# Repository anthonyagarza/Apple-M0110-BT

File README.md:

Apple M0110 BT PCB
===================

A prototype replacement pcb for the Apple M0110 keyboard. 

This pcb uses the Adafruit Feather 32u4 Bluefruit LE or a Teensy 2.0 controller to 
send keycodes to the connected computer. 

[Supported Layouts](http://www.keyboard-layout-editor.com/#/gists/c975f91d0443088521a6b2a949161cee)

Parts list 
=============

1. Teensy 2.0 x 1
2. Your favorite MX style switches x 60
3. 1N4148 switch diodes x 60

If you're going the bluetooth route you will need the following additional items: 
1. GPIO Expander (MCP23017-E/SP-ND) x 1
2. Lithium Ion battery x 1.  I chose the biggest I could find on [Amazon](https://www.amazon.com/gp/product/B0137IPVY6/ref=oh_aui_detailpage_o00_s00?ie=UTF8&psc=1) that fit inside the original Apple M0110 case.
3. Adafruit Bluefruit 32u4 module instead of the Teensy
4. 4.7k Ohm Resistors x4

Build Instructions
=====================

Coming Soon!

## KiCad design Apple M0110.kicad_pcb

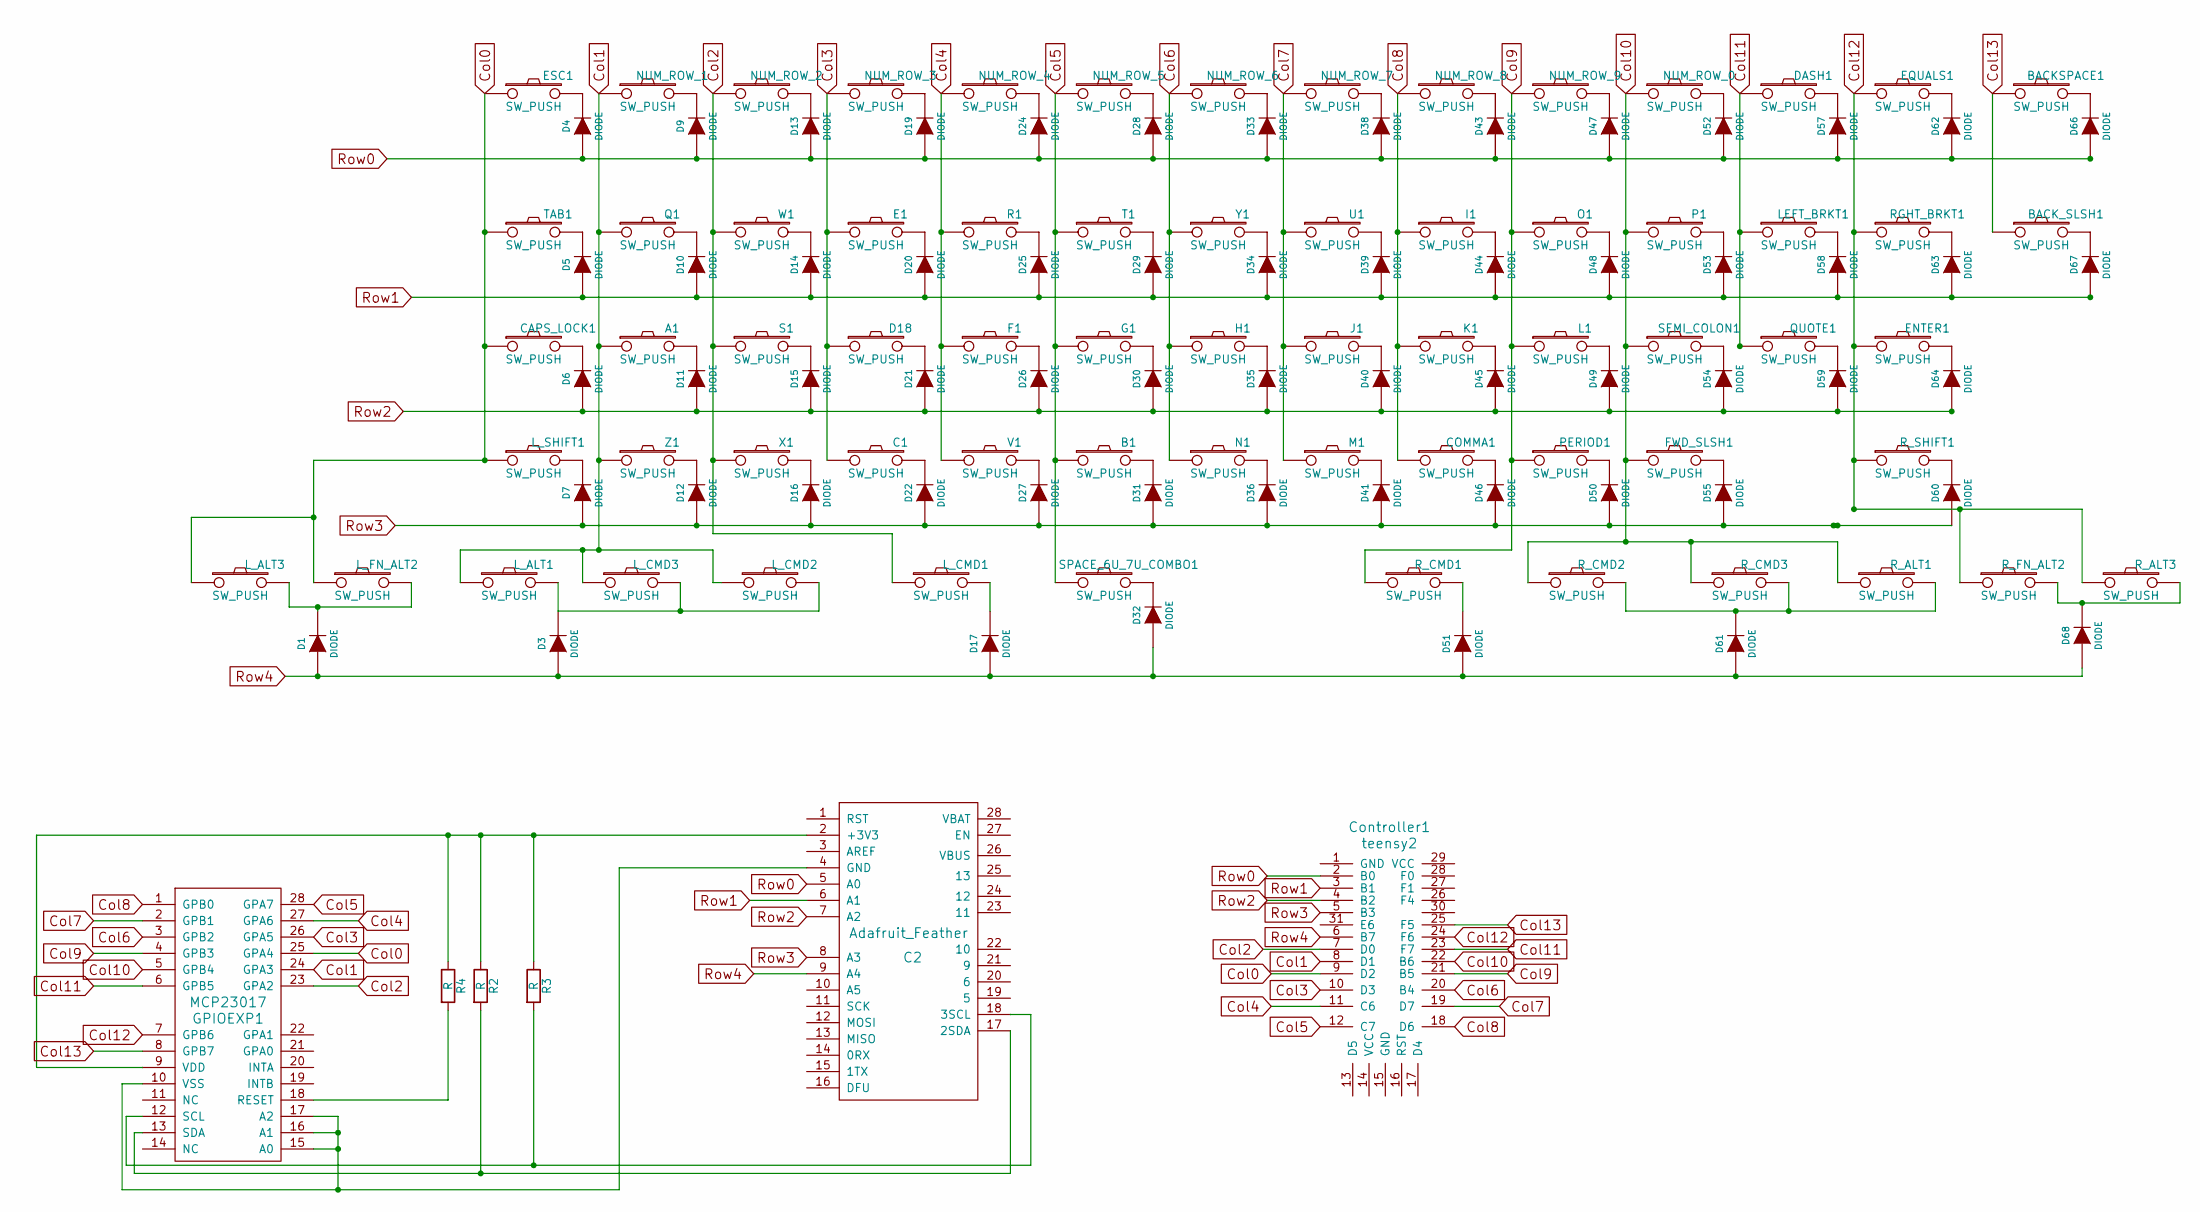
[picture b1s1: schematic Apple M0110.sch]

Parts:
A1: SW_PUSH; Hybrid_PCB_LED_100H
B1: SW_PUSH; Hybrid_PCB_LED_100H
BACKSPACE1: SW_PUSH; Hybrid_PCB_LED_100H
BACK_SLSH1: SW_PUSH; Hybrid_PCB_LED_100H
C1: SW_PUSH; Hybrid_PCB_LED_100H
C2: Adafruit_Feather; feather_32u4_bluefruit_le
CAPS_LOCK1: SW_PUSH; Hybrid_PCB_175H
COMMA1: SW_PUSH; Hybrid_PCB_LED_100H
Controller1: teensy2; Teensy_2.0
D1, D3, D4, D5, D6, D7, D9, D10, D11, D12, D13, D14, D15, D16, D17, D19, D20, D21, D22, D24, D25, D26, D27, D28, D29, D30, D31, D32, D33, D34, D35, D36, D38, D39, D40, D41, D43, D44, D45, D46, D47, D48, D49, D50, D51, D52, D53, D54, D55, D57, D58, D59, D60, D61, D62, D63, D64, D66, D67, D68: DIODE; Diode
D18: SW_PUSH; Hybrid_PCB_LED_100H
DASH1: SW_PUSH; Hybrid_PCB_LED_100H
E1: SW_PUSH; Hybrid_PCB_LED_100H
ENTER1: SW_PUSH; Hybrid_PCB_175H
EQUALS1: SW_PUSH; Hybrid_PCB_LED_100H
ESC1: SW_PUSH; Hybrid_PCB_LED_100H
F1: SW_PUSH; Hybrid_PCB_LED_100H
FWD_SLSH1: SW_PUSH; Hybrid_PCB_LED_100H
G1: SW_PUSH; Hybrid_PCB_LED_100H
GPIOEXP1: MCP23017; MCP23017-E-SP-ND
H1: SW_PUSH; Hybrid_PCB_LED_100H
I1: SW_PUSH; Hybrid_PCB_LED_100H
J1: SW_PUSH; Hybrid_PCB_LED_100H
K1: SW_PUSH; Hybrid_PCB_LED_100H
L1: SW_PUSH; Hybrid_PCB_LED_100H
LEFT_BRKT1: SW_PUSH; Hybrid_PCB_LED_100H
L_ALT1, L_ALT3: SW_PUSH; Hybrid_PCB_LED_100H
L_CMD1: SW_PUSH; Hybrid_PCB_LED_100H
L_CMD2, L_CMD3: SW_PUSH; MX_PCB_100H
L_FN_ALT2: SW_PUSH; Hybrid_PCB_LED_100H
L_SHIFT1: SW_PUSH; Hybrid_PCB_LED_225H
M1: SW_PUSH; Hybrid_PCB_LED_100H
N1: SW_PUSH; Hybrid_PCB_LED_100H
NUM_ROW_0, NUM_ROW_1, NUM_ROW_2, NUM_ROW_3, NUM_ROW_4, NUM_ROW_5, NUM_ROW_6, NUM_ROW_7, NUM_ROW_8, NUM_ROW_9: SW_PUSH; Hybrid_PCB_LED_100H
O1: SW_PUSH; Hybrid_PCB_LED_100H
P1: SW_PUSH; Hybrid_PCB_LED_100H
PERIOD1: SW_PUSH; Hybrid_PCB_LED_100H
Q1: SW_PUSH; Hybrid_PCB_LED_100H
QUOTE1: SW_PUSH; Hybrid_PCB_LED_100H
R1: SW_PUSH; Hybrid_PCB_LED_100H
R2, R3, R4: R; Resistor
RGHT_BRKT1: SW_PUSH; Hybrid_PCB_LED_100H
R_ALT1, R_ALT3: SW_PUSH; Hybrid_PCB_LED_100H
R_CMD1, R_CMD2, R_CMD3: SW_PUSH; Hybrid_PCB_LED_100H
R_FN_ALT2: SW_PUSH; Hybrid_PCB_LED_100H
R_SHIFT1: SW_PUSH; Hybrid_PCB_LED_225H
S1: SW_PUSH; Hybrid_PCB_LED_100H
SEMI_COLON1: SW_PUSH; Hybrid_PCB_LED_100H
SPACE_6U_7U_COMBO1: SW_PUSH; MX_PCB_625_7_COMBO_H
T1: SW_PUSH; Hybrid_PCB_LED_100H
TAB1: SW_PUSH; Hybrid_PCB_LED_100H
U1: SW_PUSH; Hybrid_PCB_LED_100H
V1: SW_PUSH; Hybrid_PCB_LED_100H
W1: SW_PUSH; Hybrid_PCB_LED_100H
X1: SW_PUSH; Hybrid_PCB_LED_100H
Y1: SW_PUSH; Hybrid_PCB_LED_100H
Z1: SW_PUSH; Hybrid_PCB_LED_100H

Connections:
Col0: CAPS_LOCK1.1, Controller1.9 (D2), ESC1.1, GPIOEXP1.25 (GPA4), L_ALT3.1, L_FN_ALT2.1, L_SHIFT1.1, TAB1.1
Col1: A1.1, Controller1.8 (D1), GPIOEXP1.24 (GPA3), L_ALT1.1, L_CMD2.1, L_CMD3.1, NUM_ROW_1.1, Q1.1, Z1.1
Col2: Controller1.7 (D0), GPIOEXP1.23 (GPA2), L_CMD1.1, NUM_ROW_2.1, S1.1, W1.1, X1.1
Col3: C1.1, Controller1.10 (D3), D18.1, E1.1, GPIOEXP1.26 (GPA5), NUM_ROW_3.1
Col4: Controller1.11 (C6), F1.1, GPIOEXP1.27 (GPA6), NUM_ROW_4.1, R1.1, V1.1
Col5: B1.1, Controller1.12 (C7), G1.1, GPIOEXP1.28 (GPA7), NUM_ROW_5.1, SPACE_6U_7U_COMBO1.1, T1.1
Col6: Controller1.20 (B4), GPIOEXP1.3 (GPB2), H1.1, N1.1, NUM_ROW_6.1, Y1.1
Col7: Controller1.19 (D7), GPIOEXP1.2 (GPB1), J1.1, M1.1, NUM_ROW_7.1, U1.1
Col8: COMMA1.1, Controller1.18 (D6), GPIOEXP1.1 (GPB0), I1.1, K1.1, NUM_ROW_8.1
Col9: Controller1.21 (B5), GPIOEXP1.4 (GPB3), L1.1, NUM_ROW_9.1, O1.1, PERIOD1.1, R_CMD1.1
Col10: Controller1.22 (B6), FWD_SLSH1.1, GPIOEXP1.5 (GPB4), NUM_ROW_0.1, P1.1, R_ALT1.1, R_CMD2.1, R_CMD3.1, SEMI_COLON1.1
Col11: Controller1.23 (F7), DASH1.1, GPIOEXP1.6 (GPB5), LEFT_BRKT1.1, QUOTE1.1
Col12: Controller1.24 (F6), ENTER1.1, EQUALS1.1, GPIOEXP1.7 (GPB6), RGHT_BRKT1.1, R_ALT3.1, R_FN_ALT2.1, R_SHIFT1.1
Col13: BACKSPACE1.1, BACK_SLSH1.1, Controller1.25 (F5), GPIOEXP1.8 (GPB7)
unnamed: A1.2, D11.1
unnamed: B1.2, D31.1
unnamed: BACKSPACE1.2, D66.1
unnamed: BACK_SLSH1.2, D67.1
unnamed: C1.2, D22.1
unnamed: C2.2 (+3V3), GPIOEXP1.9 (VDD), R2.1, R3.1, R4.1
unnamed: C2.4 (GND), GPIOEXP1.10 (VSS), GPIOEXP1.15 (A0), GPIOEXP1.16 (A1), GPIOEXP1.17 (A2)
unnamed: C2.17 (2SDA), GPIOEXP1.13 (SDA), R2.2
unnamed: C2.18 (3SCL), GPIOEXP1.12 (SCL), R3.2
unnamed: CAPS_LOCK1.2, D6.1
unnamed: COMMA1.2, D46.1
unnamed: D1.1, L_ALT3.2, L_FN_ALT2.2
unnamed: D3.1, L_ALT1.2, L_CMD2.2, L_CMD3.2
unnamed: D4.1, ESC1.2
unnamed: D5.1, TAB1.2
unnamed: D7.1, L_SHIFT1.2
unnamed: D9.1, NUM_ROW_1.2
unnamed: D10.1, Q1.2
unnamed: D12.1, Z1.2
unnamed: D13.1, NUM_ROW_2.2
unnamed: D14.1, W1.2
unnamed: D15.1, S1.2
unnamed: D16.1, X1.2
unnamed: D17.1, L_CMD1.2
unnamed: D18.2, D21.1
unnamed: D19.1, NUM_ROW_3.2
unnamed: D20.1, E1.2
unnamed: D24.1, NUM_ROW_4.2
unnamed: D25.1, R1.2
unnamed: D26.1, F1.2
unnamed: D27.1, V1.2
unnamed: D28.1, NUM_ROW_5.2
unnamed: D29.1, T1.2
unnamed: D30.1, G1.2
unnamed: D32.1, SPACE_6U_7U_COMBO1.2
unnamed: D33.1, NUM_ROW_6.2
unnamed: D34.1, Y1.2
unnamed: D35.1, H1.2
unnamed: D36.1, N1.2
unnamed: D38.1, NUM_ROW_7.2
unnamed: D39.1, U1.2
unnamed: D40.1, J1.2
unnamed: D41.1, M1.2
unnamed: D43.1, NUM_ROW_8.2
unnamed: D44.1, I1.2
unnamed: D45.1, K1.2
unnamed: D47.1, NUM_ROW_9.2
unnamed: D48.1, O1.2
unnamed: D49.1, L1.2
unnamed: D50.1, PERIOD1.2
unnamed: D51.1, R_CMD1.2
unnamed: D52.1, NUM_ROW_0.2
unnamed: D53.1, P1.2
unnamed: D54.1, SEMI_COLON1.2
unnamed: D55.1, FWD_SLSH1.2
unnamed: D57.1, DASH1.2
unnamed: D58.1, LEFT_BRKT1.2
unnamed: D59.1, QUOTE1.2
unnamed: D60.1, R_SHIFT1.2
unnamed: D61.1, R_ALT1.2, R_CMD2.2, R_CMD3.2
unnamed: D62.1, EQUALS1.2
unnamed: D63.1, RGHT_BRKT1.2
unnamed: D64.1, ENTER1.2
unnamed: D68.1, R_ALT3.2, R_FN_ALT2.2
unnamed: GPIOEXP1.18 (RESET), R4.2
Row0: C2.5 (A0), Controller1.2 (B0), D4.2, D9.2, D13.2, D19.2, D24.2, D28.2, D33.2, D38.2, D43.2, D47.2, D52.2, D57.2, D62.2, D66.2
Row1: C2.6 (A1), Controller1.3 (B1), D5.2, D10.2, D14.2, D20.2, D25.2, D29.2, D34.2, D39.2, D44.2, D48.2, D53.2, D58.2, D63.2, D67.2
Row2: C2.7 (A2), Controller1.4 (B2), D6.2, D11.2, D15.2, D21.2, D26.2, D30.2, D35.2, D40.2, D45.2, D49.2, D54.2, D59.2, D64.2
Row3: C2.8 (A3), Controller1.5 (B3), D7.2, D12.2, D16.2, D22.2, D27.2, D31.2, D36.2, D41.2, D46.2, D50.2, D55.2, D60.2
Row4: C2.9 (A4), Controller1.6 (B7), D1.2, D3.2, D17.2, D32.2, D51.2, D61.2, D68.2

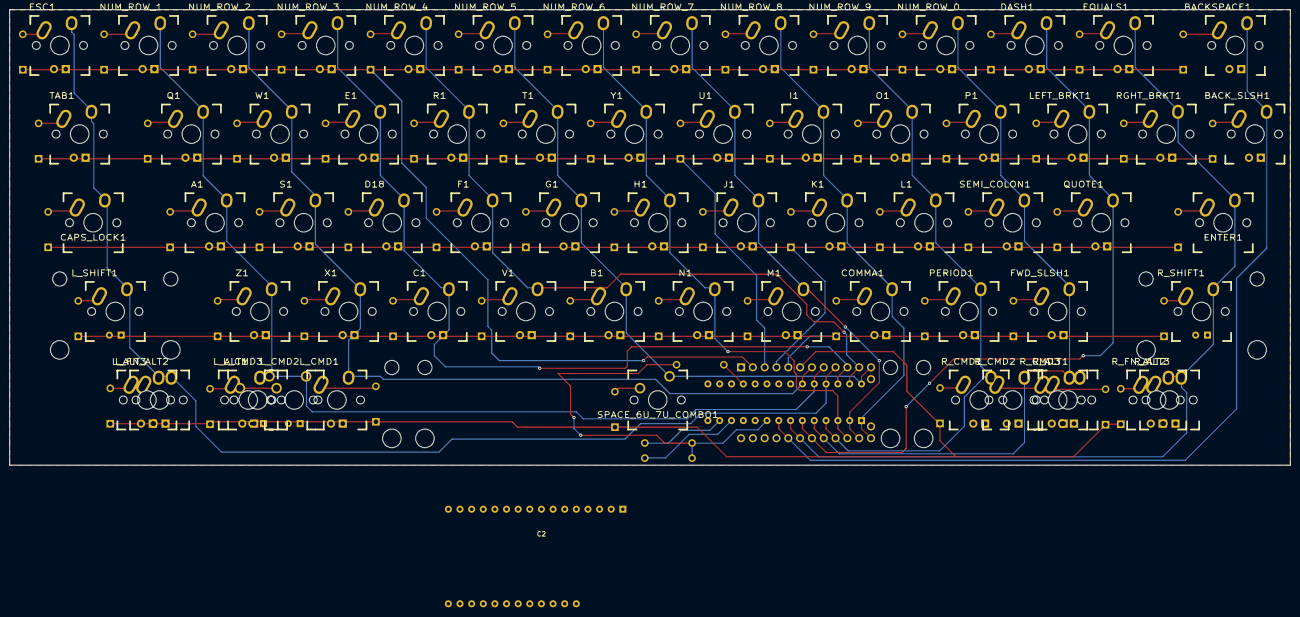
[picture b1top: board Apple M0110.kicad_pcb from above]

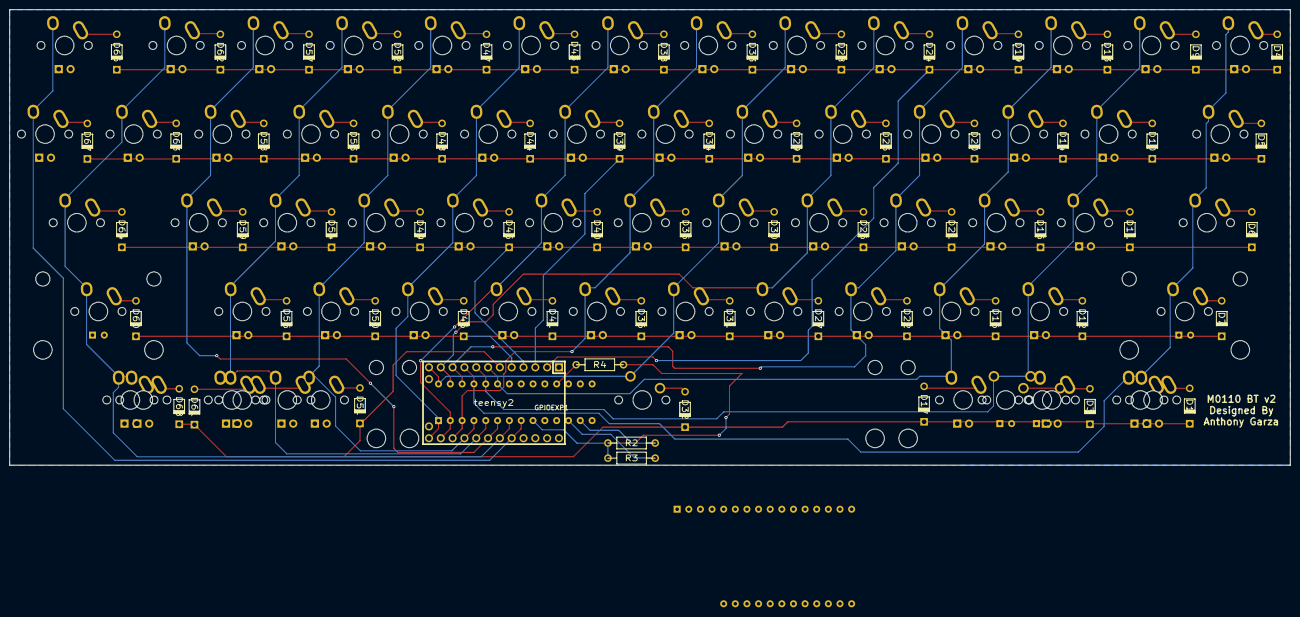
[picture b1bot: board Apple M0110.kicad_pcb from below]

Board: 2 copper layers, 275.3 x 97.9 mm, 132 parts (65 on the bottom side), 84 nets.

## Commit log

2017-03-11 Apple M0110 initial commit
    - add prototype pcb files, .gitignore, README, and License
2017-03-15 Fix the README a bit
    - remove pound signs
2018-10-11 Replace the MX only footprints with Alps + MX switch footprints
